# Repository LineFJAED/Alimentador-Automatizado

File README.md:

# Alimentador-Automatizado
Alimentador automático para mascotas domesticas como perros y gatos de todo tamaño

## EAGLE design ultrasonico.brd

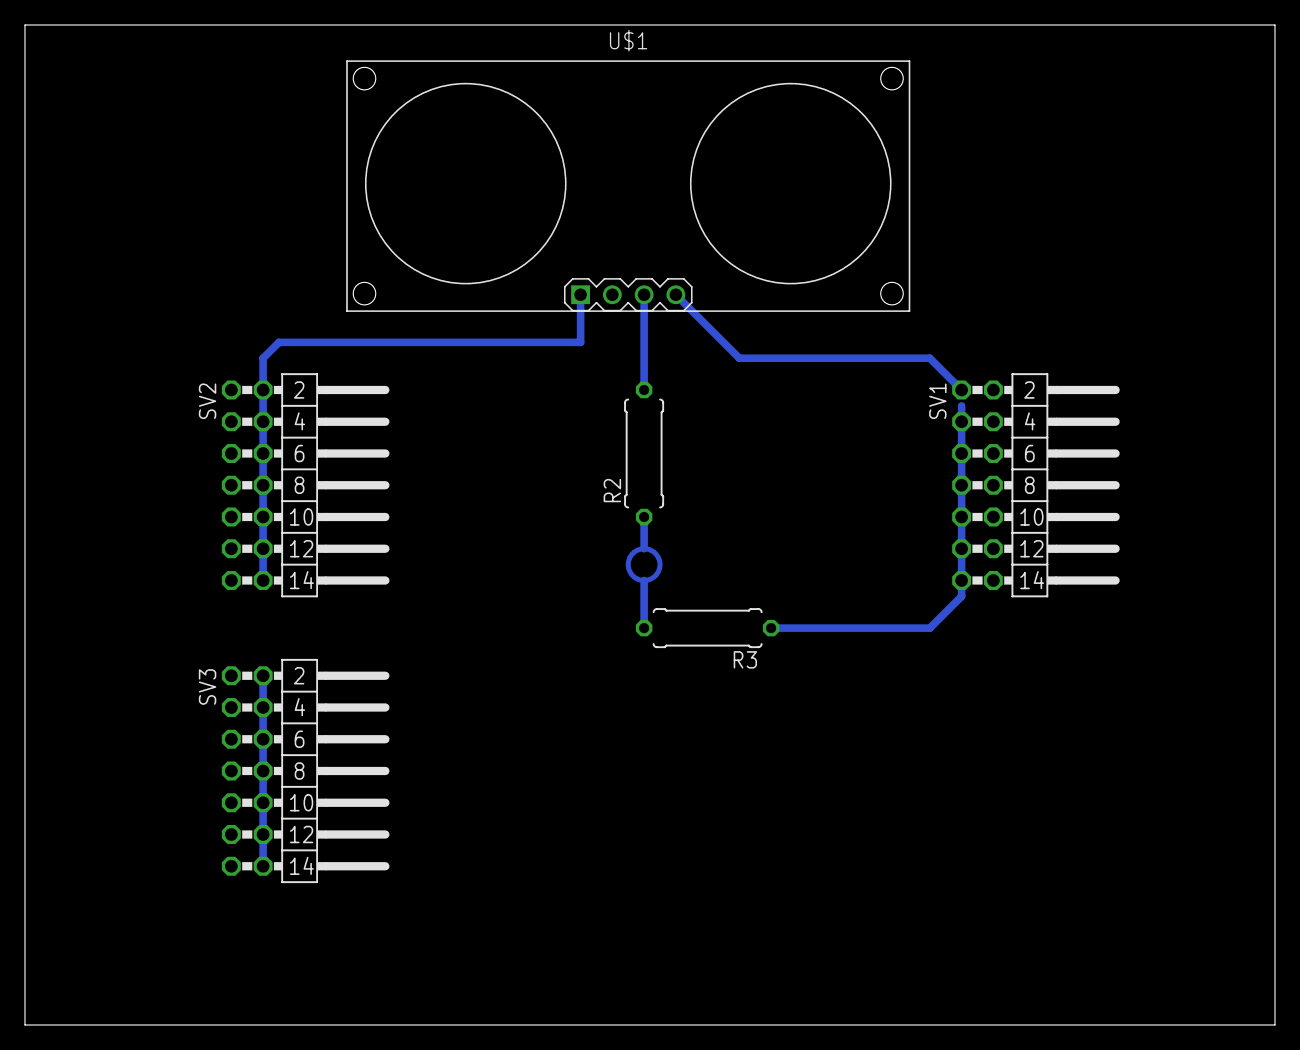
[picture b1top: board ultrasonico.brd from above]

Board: 2 copper layers, 100.0 x 80.0 mm, 6 parts (0 on the bottom side), 5 nets.

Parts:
R2, R3: 0309/10
SV1, SV2, SV3: MA07-2W
U$1: ULTRASONIC-HC-SR04

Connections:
GND: R3.1, SV1.1, SV1.3, SV1.5, SV1.7, SV1.9, SV1.11, SV1.13
unnamed: R2.2, U$1.3
unnamed: R2.1, R3.2
unnamed: SV1.12, U$1.4
VCC: SV2.2, SV2.6, SV2.8, SV2.10, SV2.12, SV2.14, SV3.2, SV3.4, SV3.6, SV3.10, SV3.12, SV3.14, U$1.1

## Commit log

2018-10-17 Plan de trabajo
    Aqui se presentan los alcances metas y demas conocimientos necesarios sobre el proyecto final de este modulo
2018-11-13 Subida de archivos finales
    Codigos, diagramas y Paper Informativo

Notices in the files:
parts and their libraries:
diy-modules: Released under the Creative Commons Attribution 4.0 International License: http://creativecommons.org/licenses/by/4.0
